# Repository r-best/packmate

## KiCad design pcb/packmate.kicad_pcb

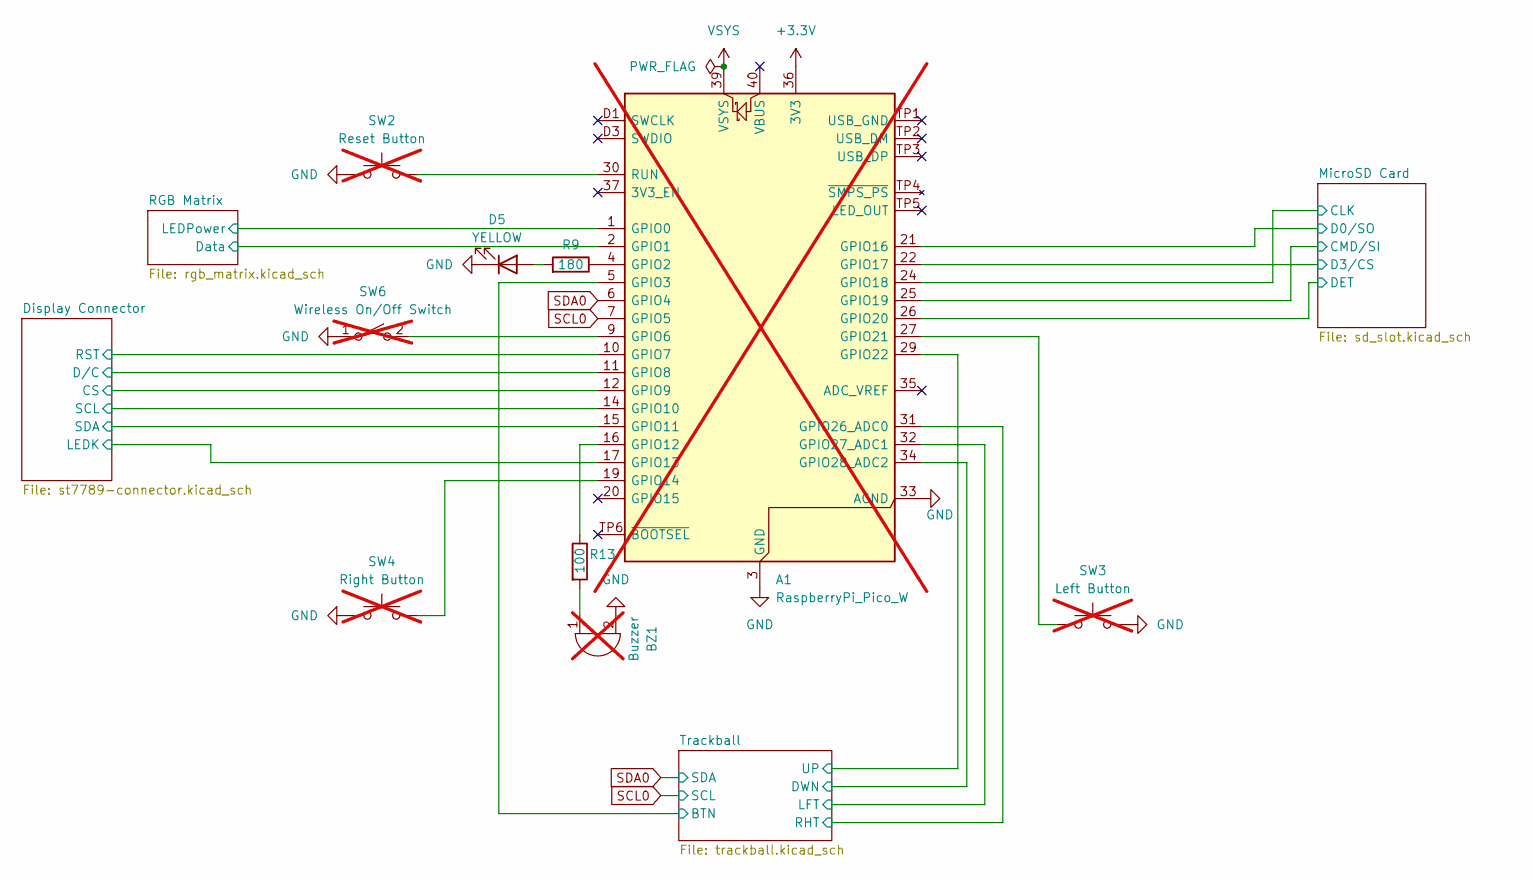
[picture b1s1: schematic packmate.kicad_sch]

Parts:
A1: RaspberryPi_Pico_W; RaspberryPi_Pico_Common_THT; not fitted
BZ1: Buzzer; Buzzer_TDK_PS1240P02BT_D12.2mm_H6.5mm; MPN PS1240P02BT; not fitted
D5: YELLOW; LED_0402_1005Metric; MPN APHHS1005SYCK
R9: 180; R_0603_1608Metric; MPN CRGCQ0603F180R
R13: 100; R_0603_1608Metric; MPN ERJ-3EKF1000V
SW2: Reset Button; SW_PUSH_6mm; MPN B3F-1000; not fitted
SW3: Left Button; SW_PUSH_6mm; MPN B3F-1000; not fitted
SW4: Right Button; SW_PUSH_6mm; MPN B3F-1000; not fitted
SW6: Wireless On/Off Switch; SW_E-Switch_EG1224_SPDT_Angled; MPN EG1224; not fitted

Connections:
+3.3V: A1.36 (3V3); also elsewhere on the board
/Display Connector/CS: A1.12 (GPIO9); also elsewhere on the board
/Display Connector/D/C: A1.11 (GPIO8); also elsewhere on the board
/Display Connector/LEDK: A1.17 (GPIO13); also elsewhere on the board
/Display Connector/RST: A1.10 (GPIO7); also elsewhere on the board
/Display Connector/SCL: A1.14 (GPIO10); also elsewhere on the board
/Display Connector/SDA: A1.15 (GPIO11); also elsewhere on the board
/MicroSD Card/CLK: A1.24 (GPIO18); also elsewhere on the board
/MicroSD Card/CMD/SI: A1.25 (GPIO19); also elsewhere on the board
/MicroSD Card/D0/SO: A1.21 (GPIO16); also elsewhere on the board
/MicroSD Card/D3/CS: A1.22 (GPIO17); also elsewhere on the board
/MicroSD Card/DET: A1.26 (GPIO20); also elsewhere on the board
/RGB Matrix/Data: A1.2 (GPIO1); also elsewhere on the board
/RGB Matrix/LEDPower: A1.1 (GPIO0); also elsewhere on the board
/Trackball/BTN: A1.5 (GPIO3); also elsewhere on the board
/Trackball/DWN: A1.34 (GPIO28_ADC2); also elsewhere on the board
/Trackball/LFT: A1.32 (GPIO27_ADC1); also elsewhere on the board
/Trackball/RHT: A1.31 (GPIO26_ADC0); also elsewhere on the board
/Trackball/UP: A1.29 (GPIO22); also elsewhere on the board
GND: A1.3 (GND), A1.8 (GND), A1.13 (GND), A1.18 (GND), A1.23 (GND), A1.28 (GND), A1.33 (AGND), A1.38 (GND), A1.D2 (GND), BZ1.2 (-), D5.1 (K), SW2.1, SW3.1, SW4.1, SW6.1 (A); also elsewhere on the board
unnamed: A1.4 (GPIO2), R9.1
unnamed: A1.9 (GPIO6), SW6.2 (B)
unnamed: A1.16 (GPIO12), R13.1
unnamed: A1.19 (GPIO14), SW4.2
unnamed: A1.27 (GPIO21), SW3.2
unnamed: A1.30 (RUN), SW2.2
unnamed: BZ1.1 (+), R13.2
unnamed: D5.2 (A), R9.2
SCL0: A1.7 (GPIO5); also elsewhere on the board
SDA0: A1.6 (GPIO4); also elsewhere on the board
VSYS: A1.39 (VSYS); also elsewhere on the board

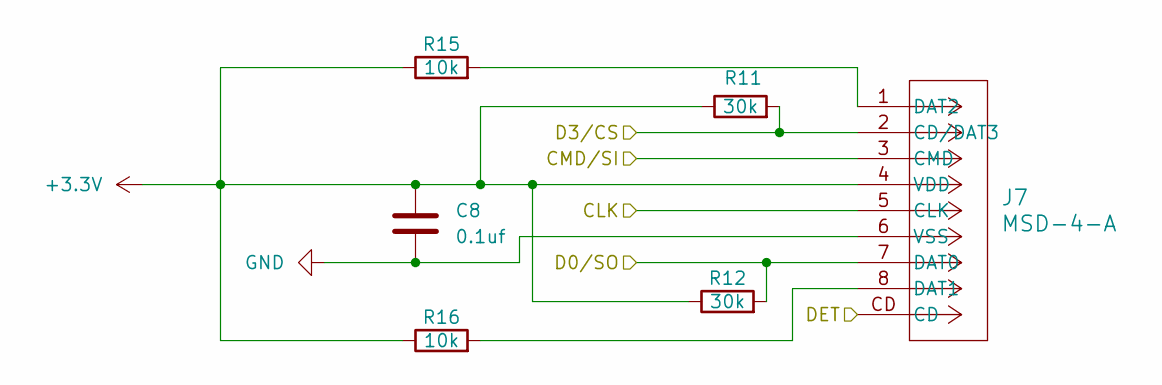
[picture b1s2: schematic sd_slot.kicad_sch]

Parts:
C8: 0.1uf; C_0402_1005Metric; MPN GRM155R71H104KE14D
J7: MSD-4-A; CONN9_MSD-4-A_SSD; MPN MSD-4-A
R11, R12: 30k; R_0603_1608Metric; MPN RC0603FR-0730KL
R15, R16: 10k; R_0603_1608Metric; MPN CRCW060310K0FKEA

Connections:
+3.3V: C8.2, J7.4 (VDD), R11.1, R12.1, R15.1, R16.1; also elsewhere on the board
/MicroSD Card/CLK: J7.5 (CLK); also elsewhere on the board
/MicroSD Card/CMD/SI: J7.3 (CMD); also elsewhere on the board
/MicroSD Card/D0/SO: J7.7 (DAT0), R12.2; also elsewhere on the board
/MicroSD Card/D3/CS: J7.2 (CD/DAT3), R11.2; also elsewhere on the board
/MicroSD Card/DET: J7.CD; also elsewhere on the board
GND: C8.1, J7.6 (VSS); also elsewhere on the board
unnamed: J7.8 (DAT1), R16.2
unnamed: J7.1 (DAT2), R15.2

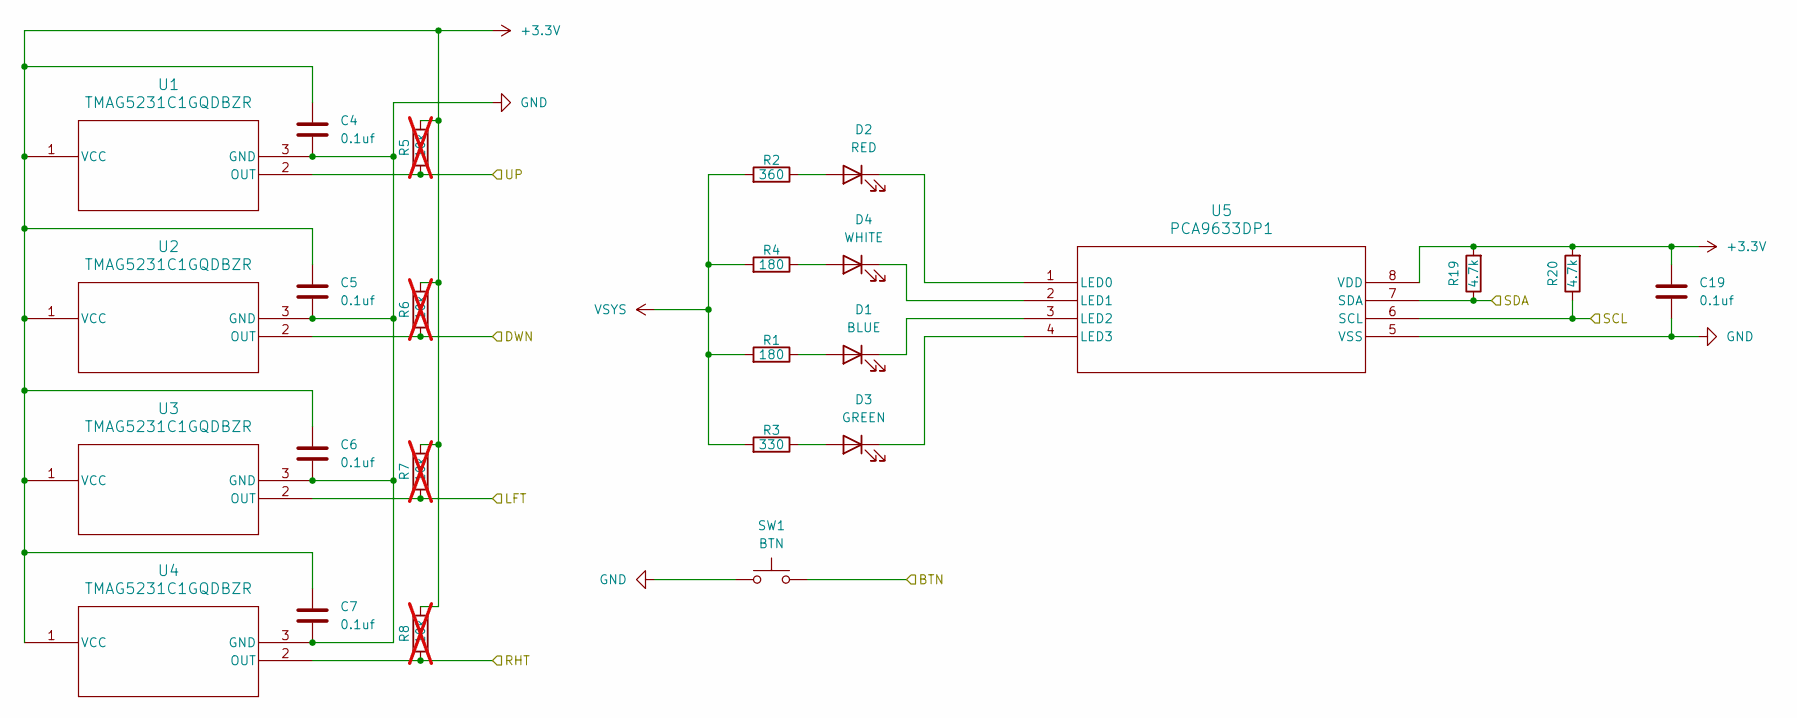
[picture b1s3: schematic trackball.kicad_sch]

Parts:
C4, C5, C6, C7, C19: 0.1uf; C_0402_1005Metric; MPN GRM155R71H104KE14D
D1: BLUE; LED_0402_1005Metric; MPN APHHS1005QBC/D
D2: RED; LED_0402_1005Metric; MPN APHHS1005SURCK
D3: GREEN; LED_0402_1005Metric; MPN APHHS1005ZGC
D4: WHITE; LED_0402_1005Metric; MPN IN-S42BT5UW
R1, R4: 180; R_0201_0603Metric; MPN RC0201FR-07180RL
R2: 360; R_0201_0603Metric; MPN RC0201FR-07360RL
R3: 330; R_0201_0603Metric; MPN RC0201FR-07330RL
R5, R6, R7, R8: 10k; R_0201_0603Metric; MPN RC0201FR-0710KL; not fitted
R19, R20: 4.7k; R_0603_1608Metric; MPN RC0603FR-074K7L
SW1: BTN; TL3315NF100Q_EWI; MPN TL3315NF100Q
U1, U2, U3, U4: TMAG5231C1GQDBZR; SOT-23-3_DBZ_TEX; MPN TMAG5231C1GQDBZR
U5: PCA9633DP1; TSSOP-8_3x3mm_P0.65mm; MPN PCA9633DP1,118

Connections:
+3.3V: C4.1, C5.1, C6.1, C7.1, C19.2, R5.2, R6.2, R7.2, R8.2, R19.2, R20.2, U1.1 (VCC), U2.1 (VCC), U3.1 (VCC), U4.1 (VCC), U5.8 (VDD); also elsewhere on the board
/Trackball/BTN: SW1.2; also elsewhere on the board
/Trackball/DWN: R6.1, U2.2 (OUT); also elsewhere on the board
/Trackball/LFT: R7.1, U3.2 (OUT); also elsewhere on the board
/Trackball/RHT: R8.1, U4.2 (OUT); also elsewhere on the board
/Trackball/UP: R5.1, U1.2 (OUT); also elsewhere on the board
GND: C4.2, C5.2, C6.2, C7.2, C19.1, SW1.1, U1.3 (GND), U2.3 (GND), U3.3 (GND), U4.3 (GND), U5.5 (VSS); also elsewhere on the board
unnamed: D1.2 (A), R1.1
unnamed: D1.1 (K), U5.3 (LED2)
unnamed: D2.2 (A), R2.1
unnamed: D2.1 (K), U5.1 (LED0)
unnamed: D3.2 (A), R3.1
unnamed: D3.1 (K), U5.4 (LED3)
unnamed: D4.2 (A), R4.1
unnamed: D4.1 (K), U5.2 (LED1)
SCL0: R20.1, U5.6 (SCL); also elsewhere on the board
SDA0: R19.1, U5.7 (SDA); also elsewhere on the board
VSYS: R1.2, R2.2, R3.2, R4.2; also elsewhere on the board

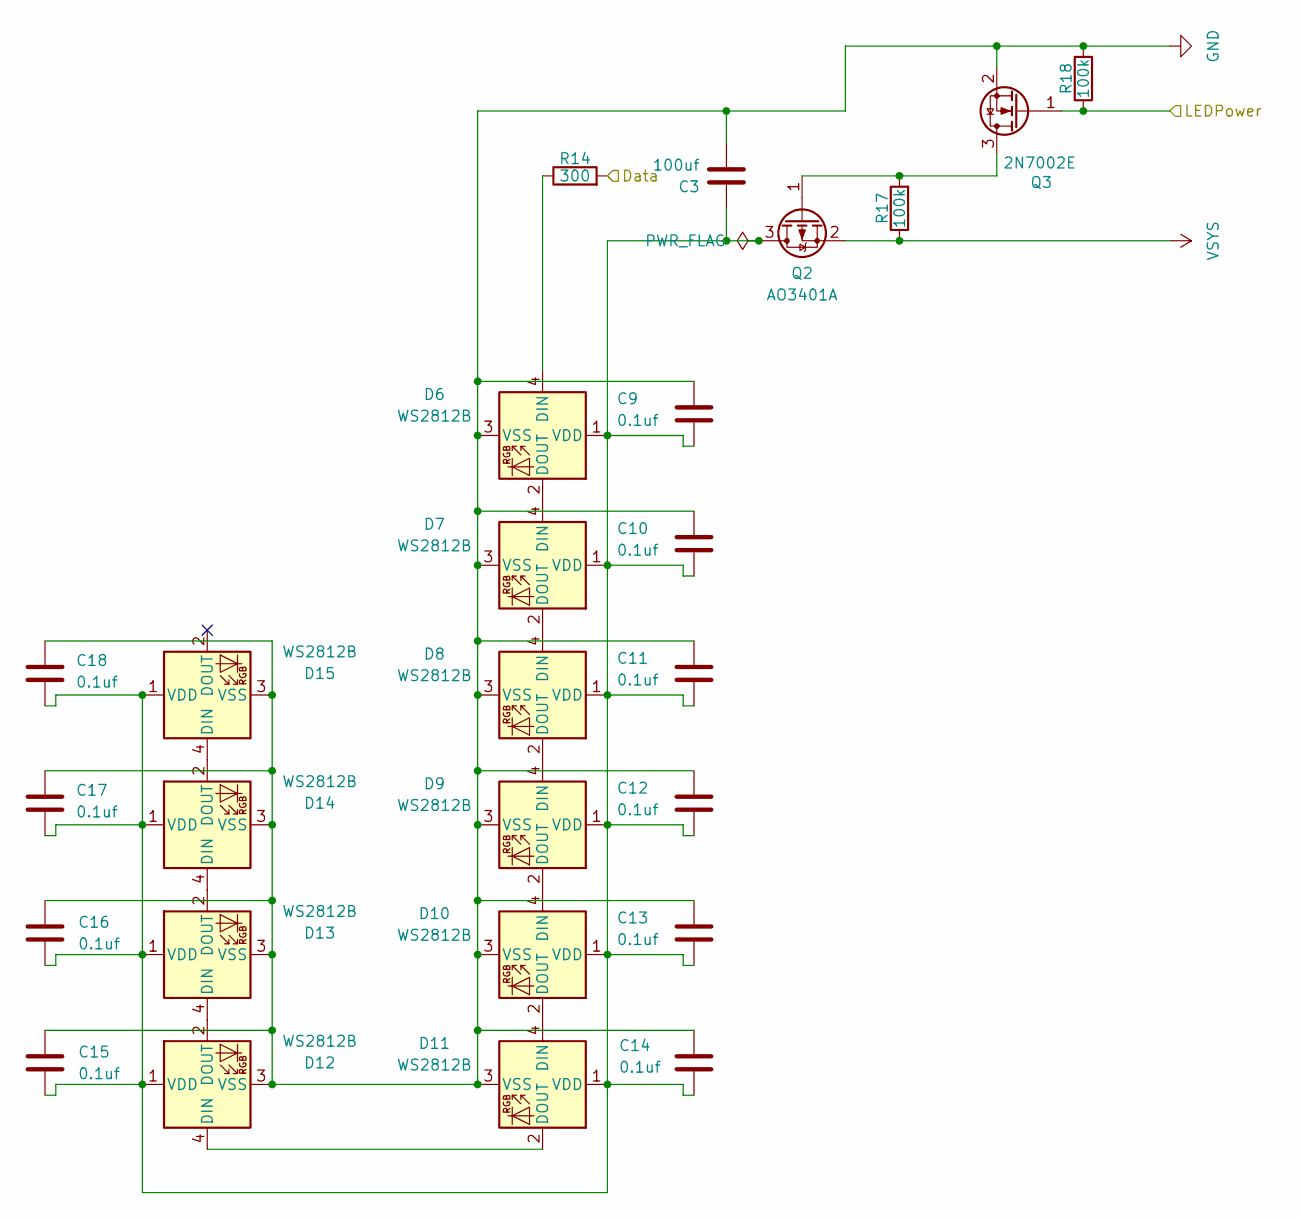
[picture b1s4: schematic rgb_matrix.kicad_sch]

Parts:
C3: 100uf; C_1206_3216Metric; MPN GRM31CR61A107MEA8L
C9, C10, C11, C12, C13, C14, C15, C16, C17, C18: 0.1uf; C_0402_1005Metric; MPN GRM155R71H104KE14D
D6, D7, D8, D9, D10, D11, D12, D13, D14, D15: WS2812B; LED_WS2812B_PLCC4_5.0x5.0mm_P3.2mm; MPN WS2812B
Q2: AO3401A; SOT-23; MPN AO3401A
Q3: 2N7002E; SOT-23; MPN 2N7002E-7-F
R14: 300; R_0603_1608Metric; MPN ERJ-3GEYJ301V
R17, R18: 100k; R_0603_1608Metric; MPN CRCW0603100KFKEA

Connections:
/RGB Matrix/Data: R14.2; also elsewhere on the board
/RGB Matrix/LEDPower: Q3.1 (G), R18.1; also elsewhere on the board
GND: C3.2, C9.1, C10.1, C11.1, C12.1, C13.1, C14.1, C15.1, C16.1, C17.1, C18.1, D6.3 (VSS), D7.3 (VSS), D8.3 (VSS), D9.3 (VSS), D10.3 (VSS), D11.3 (VSS), D12.3 (VSS), D13.3 (VSS), D14.3 (VSS), D15.3 (VSS), Q3.2 (S), R18.2; also elsewhere on the board
unnamed: D6.4 (DIN), R14.1
unnamed: D6.2 (DOUT), D7.4 (DIN)
unnamed: D7.2 (DOUT), D8.4 (DIN)
unnamed: D8.2 (DOUT), D9.4 (DIN)
unnamed: D9.2 (DOUT), D10.4 (DIN)
unnamed: D10.2 (DOUT), D11.4 (DIN)
unnamed: C3.1, C9.2, C10.2, C11.2, C12.2, C13.2, C14.2, C15.2, C16.2, C17.2, C18.2, D6.1 (VDD), D7.1 (VDD), D8.1 (VDD), D9.1 (VDD), D10.1 (VDD), D11.1 (VDD), D12.1 (VDD), D13.1 (VDD), D14.1 (VDD), D15.1 (VDD), Q2.3 (D)
unnamed: D11.2 (DOUT), D12.4 (DIN)
unnamed: D12.2 (DOUT), D13.4 (DIN)
unnamed: D13.2 (DOUT), D14.4 (DIN)
unnamed: D14.2 (DOUT), D15.4 (DIN)
unnamed: Q2.1 (G), Q3.3 (D), R17.2
VSYS: Q2.2 (S), R17.1; also elsewhere on the board

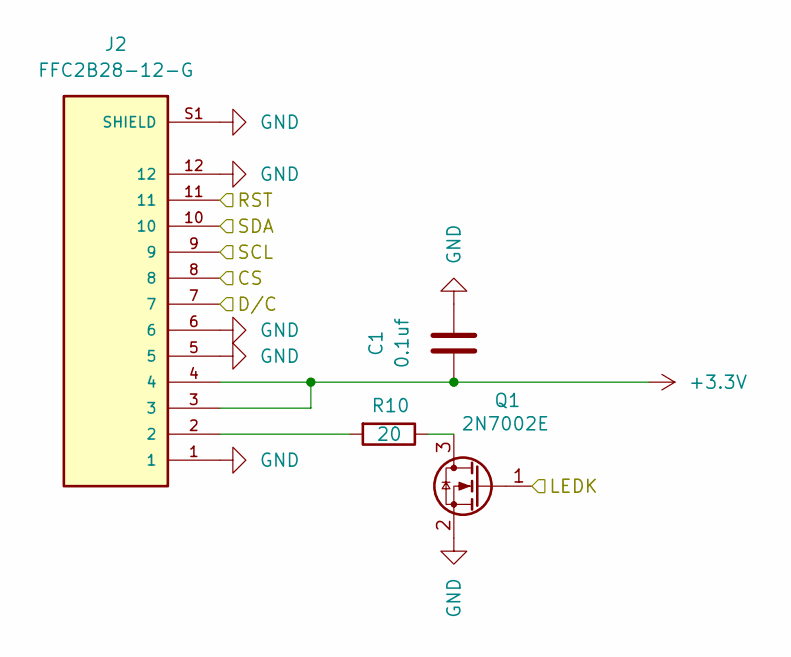
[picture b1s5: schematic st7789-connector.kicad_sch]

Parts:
C1: 0.1uf; C_0402_1005Metric; MPN GRM155R71H104KE14D
J2: FFC2B28-12-G; GCT_FFC2B28-12-G; MPN FFC2B28-12-G; DigiKey_Part_Number 2073-FFC2B28-12-GCT-ND
Q1: 2N7002E; SOT-23; MPN 2N7002E-7-F
R10: 20; R_0603_1608Metric; MPN RMCF0603JT20R0

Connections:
+3.3V: C1.2, J2.3, J2.4; also elsewhere on the board
/Display Connector/CS: J2.8; also elsewhere on the board
/Display Connector/D/C: J2.7; also elsewhere on the board
/Display Connector/LEDK: Q1.1 (G); also elsewhere on the board
/Display Connector/RST: J2.11; also elsewhere on the board
/Display Connector/SCL: J2.9; also elsewhere on the board
/Display Connector/SDA: J2.10; also elsewhere on the board
GND: C1.1, J2.1, J2.5, J2.6, J2.12, J2.S1 (SHIELD), J2.S2 (SHIELD), Q1.2 (S); also elsewhere on the board
unnamed: J2.2, R10.2
unnamed: Q1.3 (D), R10.1

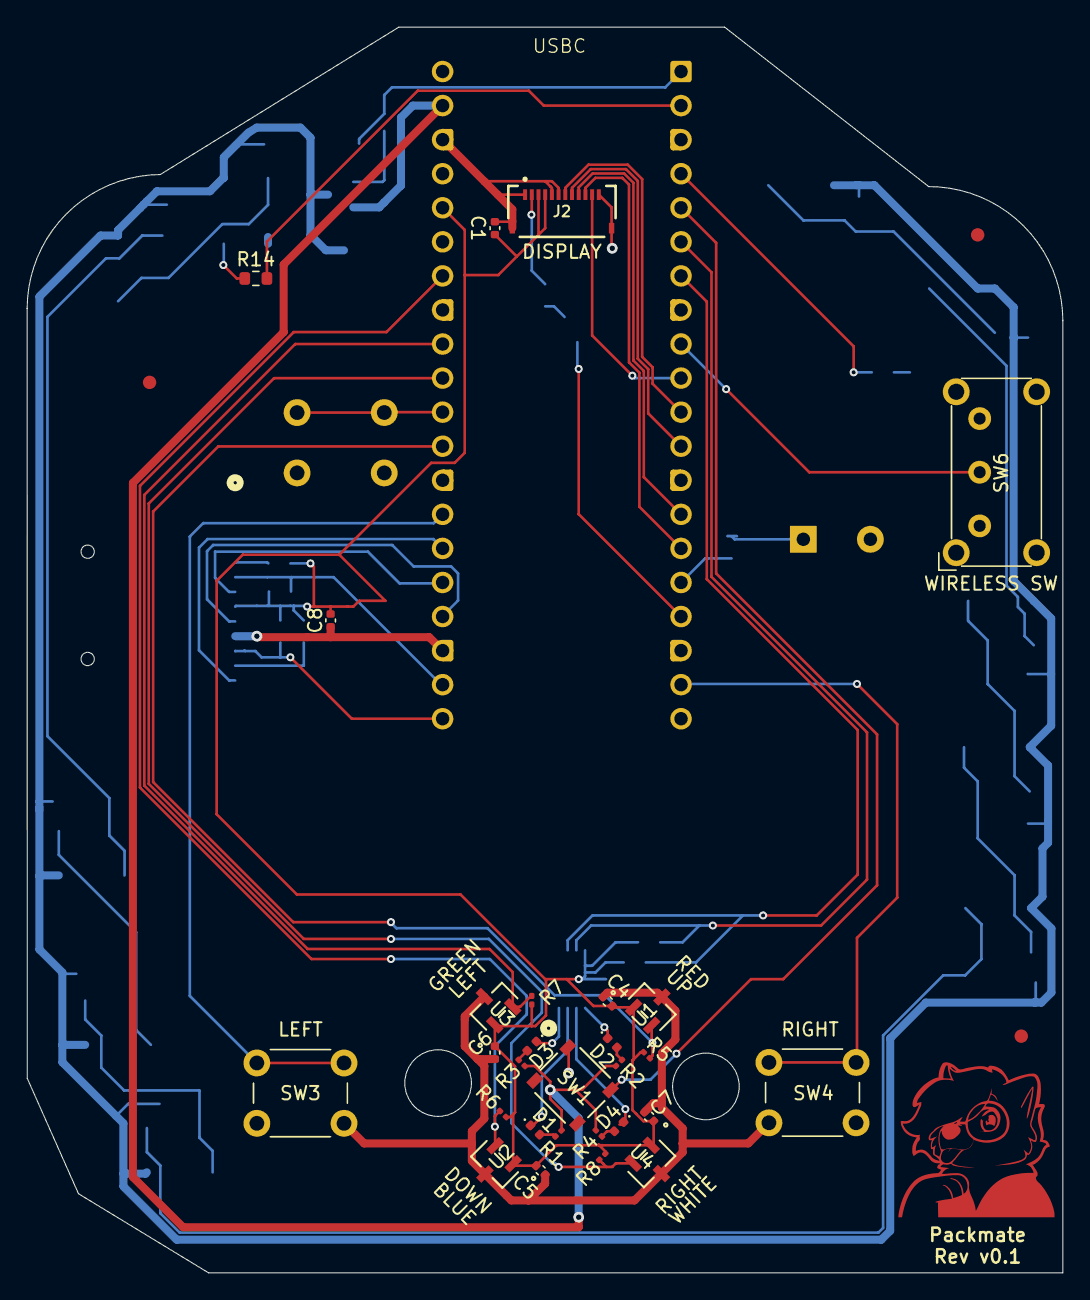
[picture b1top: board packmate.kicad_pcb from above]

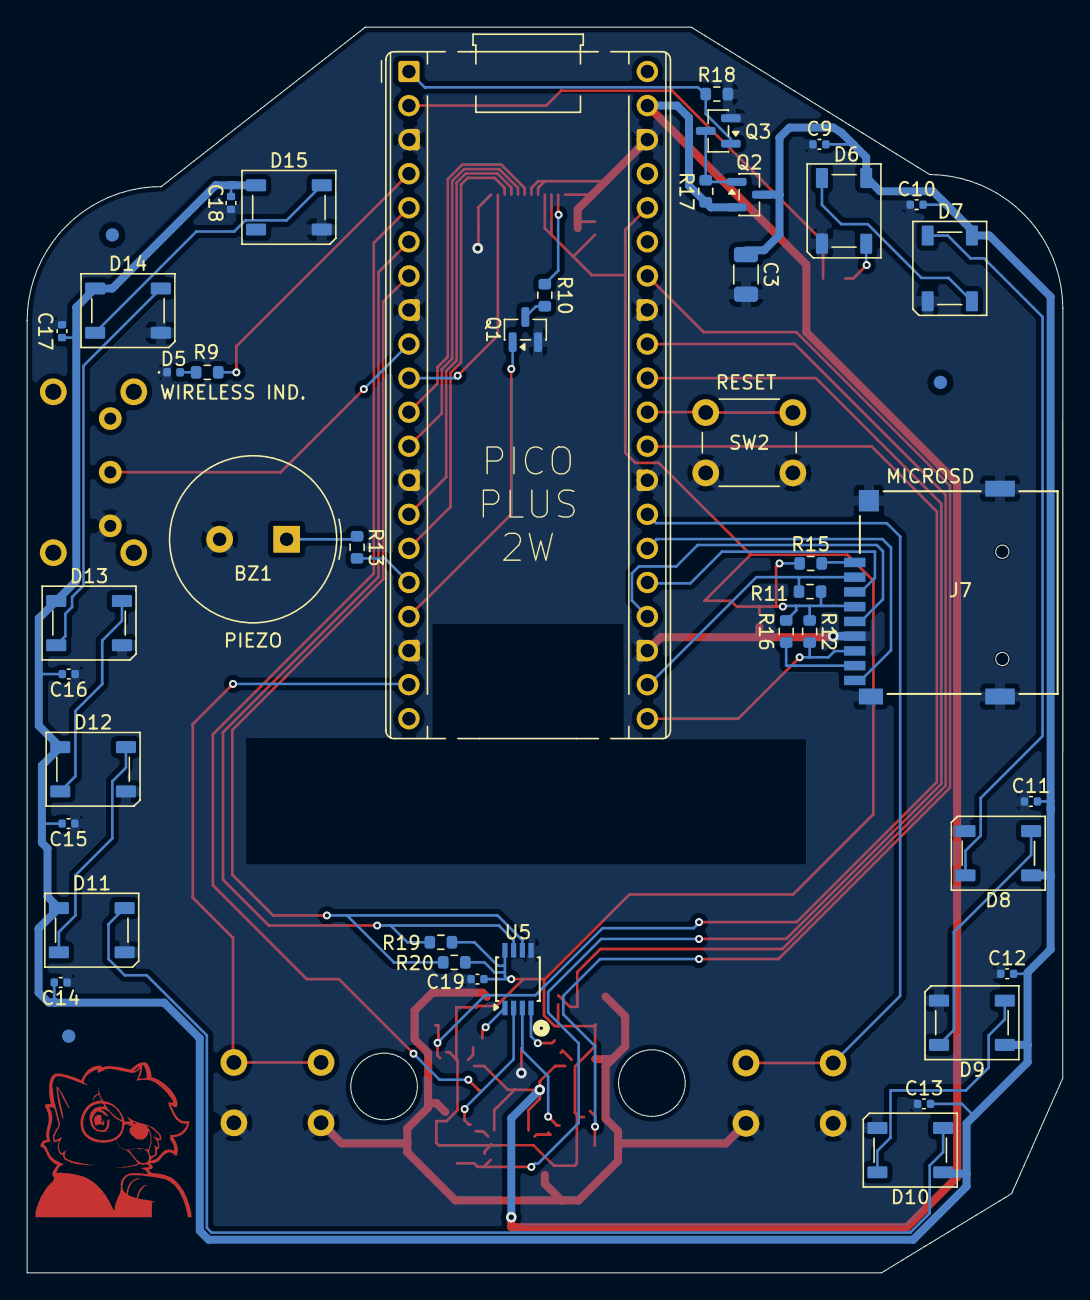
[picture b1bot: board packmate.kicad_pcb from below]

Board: 2 copper layers, 77.2 x 92.9 mm, 76 parts (45 on the bottom side), 55 nets.

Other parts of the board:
FID1, FID2, FID3, FID4, FID5, FID6: Fiducial_1mm_Mask2mm

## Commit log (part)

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2026-04-11 We're cooking chat (added mutlicore, sprite loading w/ reserved memory slots, buzzer)
2026-04-12 Adding screen manager and reorganizing stuff
2026-04-12 Adding kicad empty project, will need to learn how this works later
2026-04-15 Moving sd impl into hardware
2026-04-15 Moving screen impl to hardware and renaming lcd
2026-04-15 Moving buzzer impl to hardware
2026-04-15 Adding boot screen
2026-04-24 Updating screen management to support fps/event screen types
2026-04-24 Fixing rgb matrix init issue (keep all i2c on core 0)
2026-04-24 Fix rgb startup flash
2026-04-24 Fixing some flicker issues and completing boot screen logic
2026-04-25 Screen transistions are finally fully working
2026-04-25 Adding new sprites but they're kinda fucked because they're solid black with transparency, code doesn't support transparency yet
2026-04-25 Adding widgets and menu screen is basically functional
2026-05-01 Implementing LRU cache for sprites
2026-05-02 Adding memory usage bar to menu
2026-05-03 Vastly improving the update-render loop
2026-05-03 Implementing watchdog for crash handling
2026-05-03 Moving watchdog impl to namespace, to be expanded with crash data
2026-05-03 Adding watchdog info to error screen
2026-05-04 Moving hardware to namespaces for better organization
2026-05-05 Adding ram usage text
2026-05-13 Adding placeholder for partial_update
2026-05-15 Moving sprite storage to psram (so much space now!)
2026-05-15 Moving memory usage widget to new debug screen, accessible via trackball long press
2026-05-15 Setting up x macro for sprite path registry
2026-05-15 Enabling sprite transparency
2026-05-16 Intermediate commit
2026-05-16 Big sprite pool refactor, supporting animations now?
2026-05-16 Adding frame support to draw_sprite
2026-05-28 Animating sprites
2026-05-30 Updating LCD init for new screen, required some extra commands
2026-06-01 Moving to rgb565 for better color definition
2026-06-01 Forgot a file in my commit somehow
2026-06-01 Reorganizing hardware directory, all those folders were messy
